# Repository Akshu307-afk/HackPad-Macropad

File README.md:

# CodePad :joystick:
This is a customized macro pad by me.
It is designed for coding shortcuts and as a music controller. 

# Features :sparkles:
 * This has a 3x4 MacroPad that uses a rotary encoder and an OLED Display and uses [QMK](https://qmk.fm/) firmware.
 * 128x32 OLED Display
 * EC11 Rotary encoder for its thing to do (LOL)
* 12 Keys

# Firmware overview
This hackpad uses QMK firmware for everything.

 - The rotary encoder changes volume. Press to mute
 - The 4 keys currently act as macros.
 - The OLED displays the current song that you are playing

# Proccess :fire:
I started the macro pad around 5 days ago. I started with the guide; first, I was following every single guide then after seeing other's macropad's i also thought i will also add some more components so it will look good and a bit better for me. Then I started with the schematic; it was a bit hard, but everything went well. Then came the PCB. The hardest part was the routing(that was the second time doing a PCB all by myself). I got so frustrated, so I installed this app on my laptop called Freerouting, which did the hard work for me in seconds. I felt relief. Then the 3rd hardest challenge came for me: designing the case in Fusion 360. I sat for 5-6 hrs(I did not record it cause i did not know that we could record)and was halfway done. Today[10/22/2026], I finished the CAD project and my firmware. I was so excited for the outcome. This evening I made my rep in my github which is this. It also took me some time. That's all!!!

# Bom
* 12x Cherry MX Switches
* 12x DSA Keycaps
* 4x M3x5x4 Heatset inserts
* 4x M3x16mm SHCS Bolts
* 4X M3x12mm SHCS Bolts
* 13x 1N4148 DO-35 Diodes.
* 1x 0.91" 128x32 OLED Display
* 1x EC11 Rotary Encoder
* 1x XIAO RP2040
* 1x Case

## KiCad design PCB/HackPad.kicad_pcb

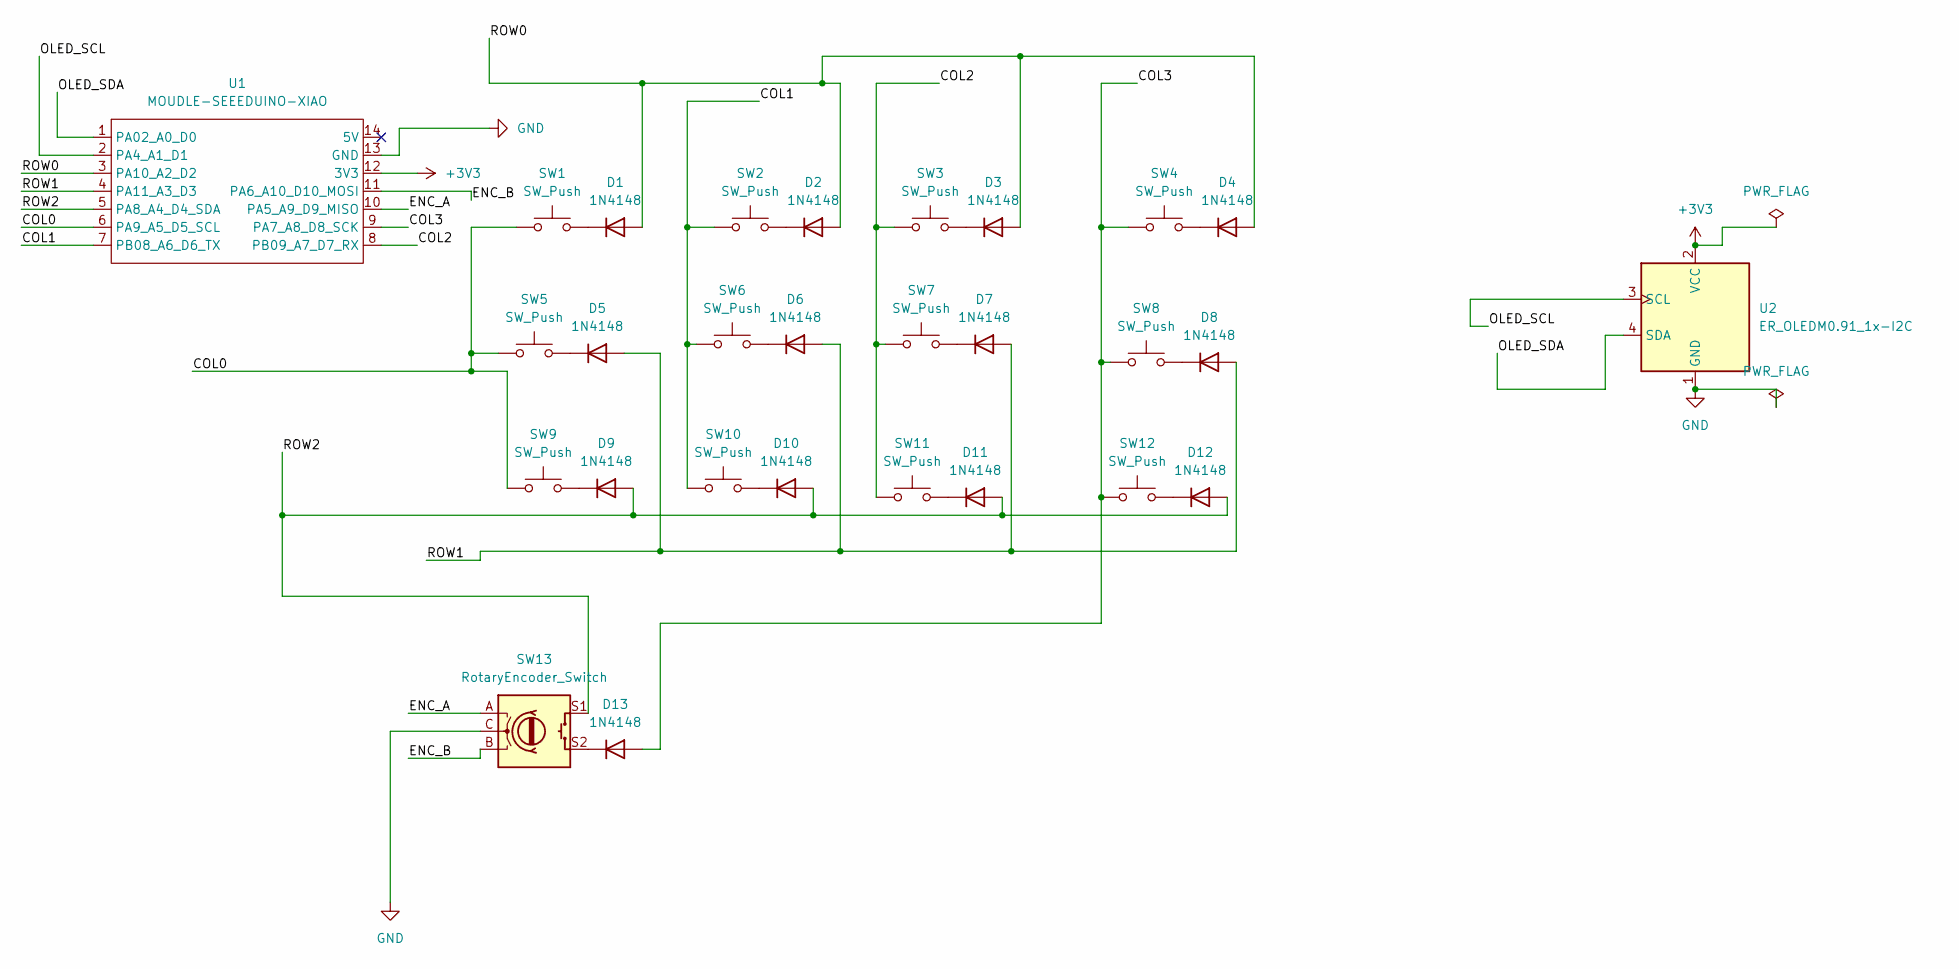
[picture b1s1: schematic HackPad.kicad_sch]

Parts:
D1, D2, D3, D4, D5, D6, D7, D8, D9, D10, D11, D12, D13: 1N4148; D_DO-35_SOD27_P7.62mm_Horizontal
SW1, SW2, SW3, SW4, SW5, SW6, SW7, SW8, SW9, SW10, SW11, SW12: SW_Push; SW_Cherry_MX_1.00u_PCB
SW13: RotaryEncoder_Switch; RotaryEncoder_Alps_EC11E-Switch_Vertical_H20mm
U1: MOUDLE-SEEEDUINO-XIAO; XIAO-Generic-Hybrid-14P-2.54-21X17.8MM
U2: ER_OLEDM0.91_1x-I2C

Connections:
+3V3: U1.12 (3V3), U2.2 (VCC)
/COL0: SW1.1, SW5.1, SW9.1, U1.6 (PA9_A5_D5_SCL)
/COL1: SW2.1, SW6.1, SW10.1, U1.7 (PB08_A6_D6_TX)
/COL2: SW3.1, SW7.1, SW11.1, U1.8 (PB09_A7_D7_RX)
/COL3: D13.2 (A), SW4.1, SW8.1, SW12.1, U1.9 (PA7_A8_D8_SCK)
/ENC_A: SW13.A, U1.10 (PA5_A9_D9_MISO)
/ENC_B: SW13.B, U1.11 (PA6_A10_D10_MOSI)
/OLED_SCL: U1.2 (PA4_A1_D1), U2.3 (SCL)
/OLED_SDA: U1.1 (PA02_A0_D0), U2.4 (SDA)
/ROW0: D1.2 (A), D2.2 (A), D3.2 (A), D4.2 (A), U1.3 (PA10_A2_D2)
/ROW1: D5.2 (A), D6.2 (A), D7.2 (A), D8.2 (A), U1.4 (PA11_A3_D3)
/ROW2: D9.2 (A), D10.2 (A), D11.2 (A), D12.2 (A), SW13.S1, U1.5 (PA8_A4_D4_SDA)
GND: SW13.C, U1.13 (GND), U2.1 (GND)
unnamed: D1.1 (K), SW1.2
unnamed: D2.1 (K), SW2.2
unnamed: D3.1 (K), SW3.2
unnamed: D4.1 (K), SW4.2
unnamed: D5.1 (K), SW5.2
unnamed: D6.1 (K), SW6.2
unnamed: D7.1 (K), SW7.2
unnamed: D8.1 (K), SW8.2
unnamed: D9.1 (K), SW9.2
unnamed: D10.1 (K), SW10.2
unnamed: D11.1 (K), SW11.2
unnamed: D12.1 (K), SW12.2
unnamed: D13.1 (K), SW13.S2

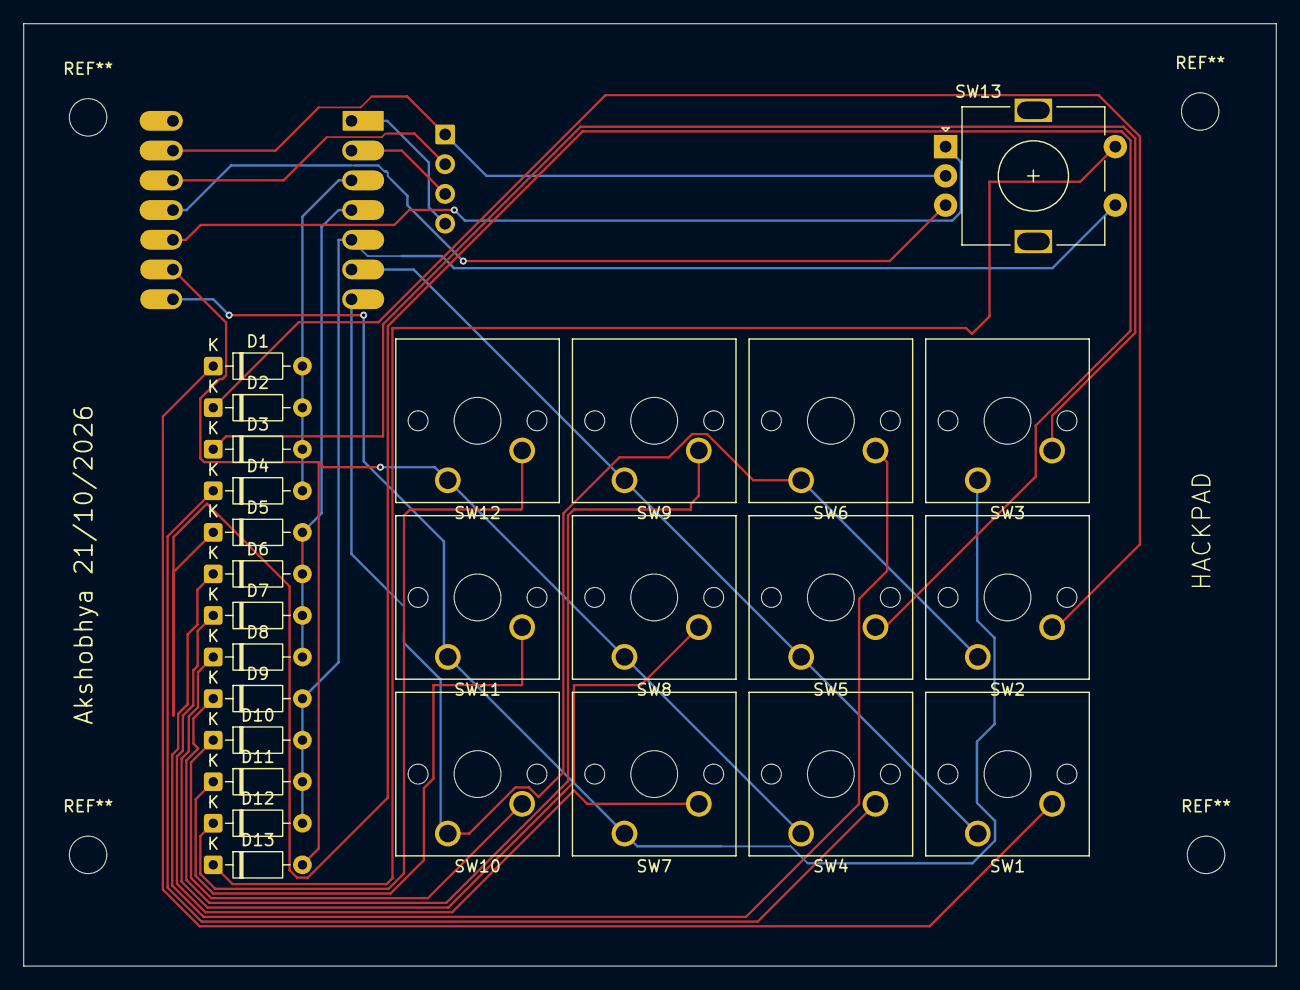
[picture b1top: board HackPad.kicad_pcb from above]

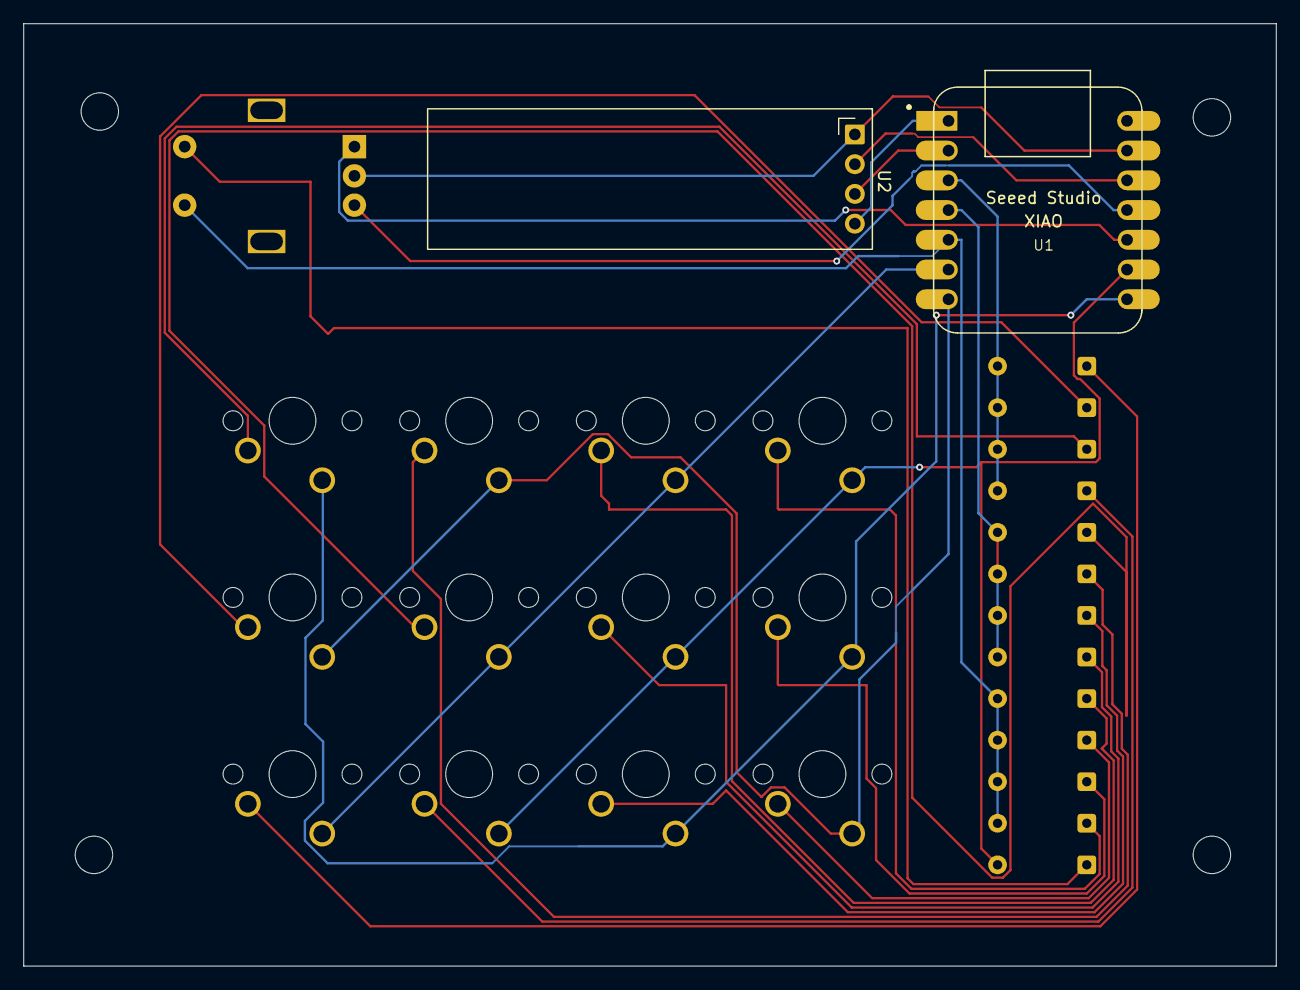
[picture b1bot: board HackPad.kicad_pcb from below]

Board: 2 copper layers, 107.0 x 80.5 mm, 28 parts (2 on the bottom side), 26 nets.
